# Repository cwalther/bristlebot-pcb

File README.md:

# Capacitor-Powered Bristlebot Kit

Eagle PCB files for
[http://wiki.fablabwinti.ch/Capacitor-Powered_Bristlebot_Kit](http://wiki.fablabwinti.ch/Capacitor-Powered_Bristlebot_Kit).

© 2016 Christian Walther, licensed [CC BY-SA 4.0](http://creativecommons.org/licenses/by-sa/4.0/).

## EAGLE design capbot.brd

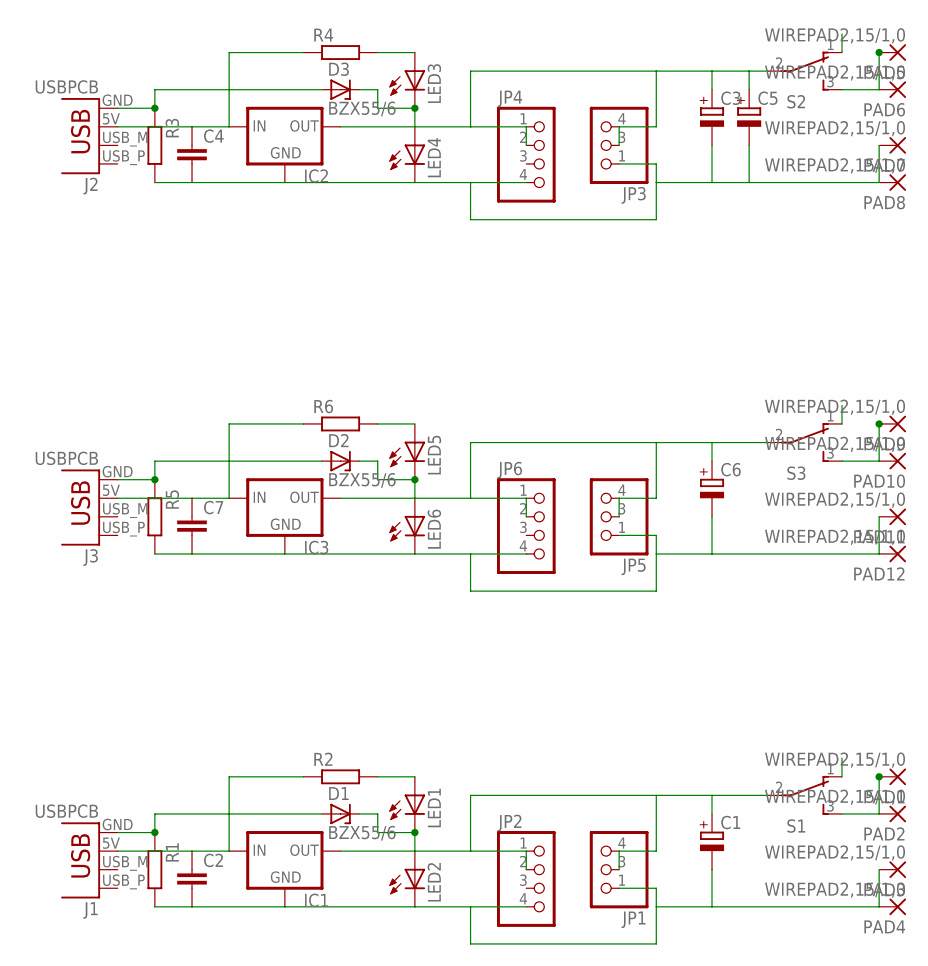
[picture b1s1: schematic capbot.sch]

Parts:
C1, C3, C5, C6: CPOL-EUE5-10.5; E5-10,5
C2, C4, C7: C-EUC1206; C1206
D1, D2, D3: BZX55/6; DO35Z6
IC1, IC2, IC3: MCP1700INLINE; TO92-INLINE
J1, J2, J3: USBPCB; USB-A-PCB
JP1, JP3, JP5: PINHD-1X3-4GAP; 1X04/GAP2
JP2, JP4, JP6: PINHD-1X4; 1X04/OFFSETDOWN
LED1, LED2, LED3, LED4, LED5, LED6: LED3MM-MOREFLAT
PAD1, PAD2, PAD3, PAD4, PAD5, PAD6, PAD7, PAD8, PAD9, PAD10, PAD11, PAD12: WIREPAD2,15/1,0; 2,15/1,0
R1, R2, R3, R4, R5, R6: R-EU_0207/7; 0207/7
S1, S2, S3: TL36PO; TL3XPO

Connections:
unnamed: C1.-, C2.2, IC1.1 (GND), JP1.1, JP2.4, LED2.K (C), PAD3.1, PAD4.1, R1.2
unnamed: C1.+, IC1.3 (OUT), JP1.3 (2), JP1.4 (3), JP2.1, JP2.2, S1.2
unnamed: PAD1.1, PAD2.1, S1.3 (S)
unnamed: D1.A, J1.GND, R1.1
unnamed: C2.1, IC1.2 (IN), J1.5V (VBUS), R2.1
unnamed: LED1.A, R2.2
unnamed: D1.C, LED1.K (C), LED2.A
unnamed: C3.-, C4.2, C5.-, IC2.1 (GND), JP3.1, JP4.4, LED4.K (C), PAD7.1, PAD8.1, R3.2
unnamed: C3.+, C5.+, IC2.3 (OUT), JP3.3 (2), JP3.4 (3), JP4.1, JP4.2, S2.2
unnamed: PAD5.1, PAD6.1, S2.3 (S)
unnamed: D3.A, J2.GND, R3.1
unnamed: C4.1, IC2.2 (IN), J2.5V (VBUS), R4.1
unnamed: LED3.A, R4.2
unnamed: D3.C, LED3.K (C), LED4.A
unnamed: C6.-, C7.2, IC3.1 (GND), JP5.1, JP6.4, LED6.K (C), PAD11.1, PAD12.1, R5.2
unnamed: C6.+, IC3.3 (OUT), JP5.3 (2), JP5.4 (3), JP6.1, JP6.2, S3.2
unnamed: PAD9.1, PAD10.1, S3.3 (S)
unnamed: D2.A, J3.GND, R5.1
unnamed: C7.1, IC3.2 (IN), J3.5V (VBUS), R6.1
unnamed: LED5.A, R6.2
unnamed: D2.C, LED5.K (C), LED6.A

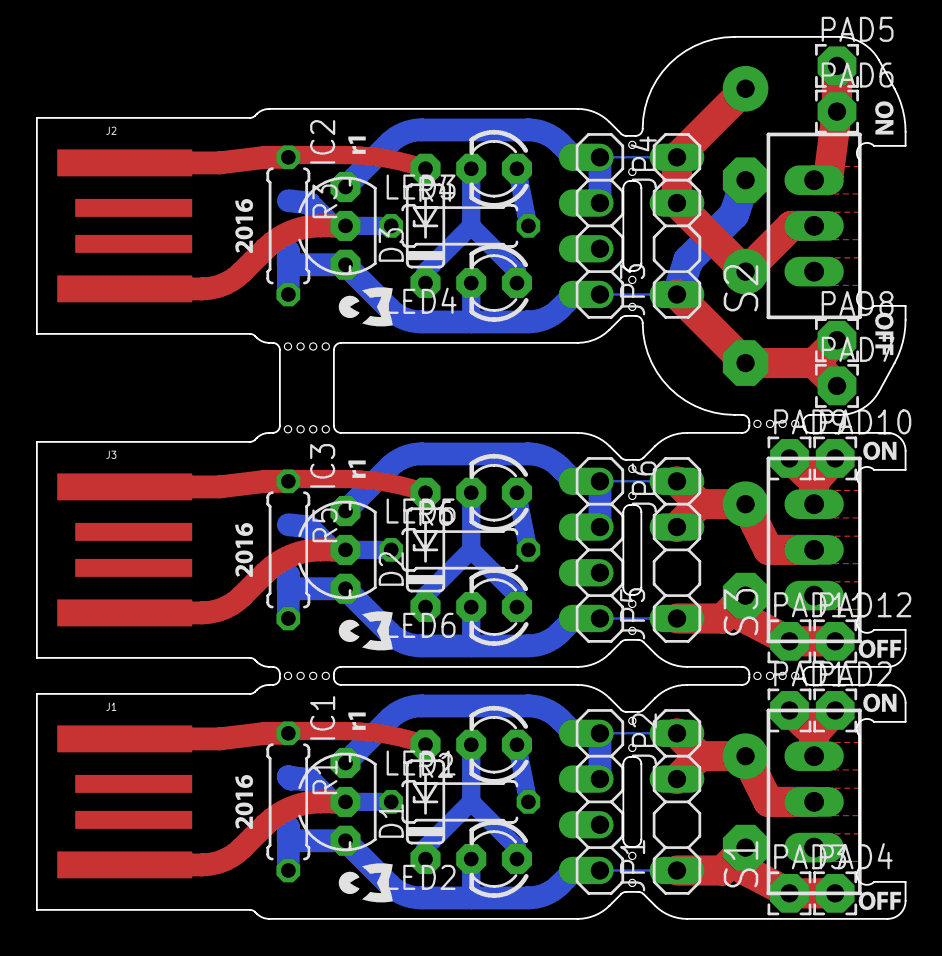
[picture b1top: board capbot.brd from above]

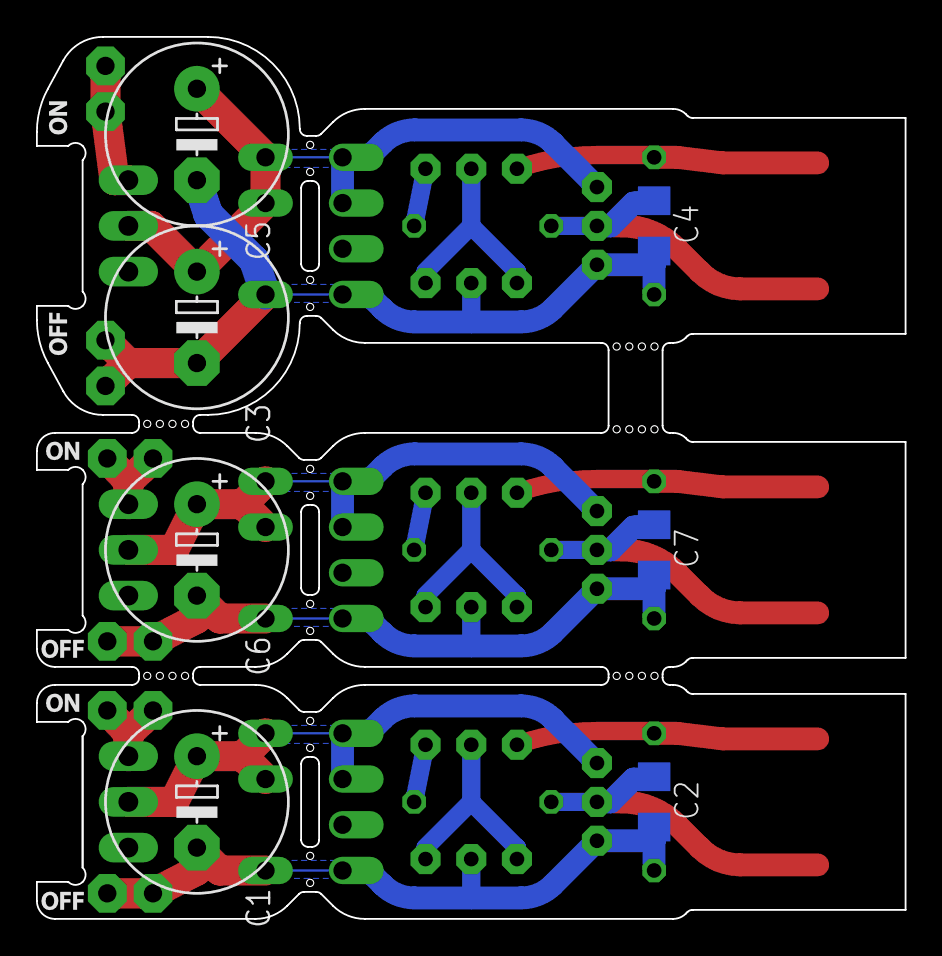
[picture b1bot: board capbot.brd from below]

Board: 2 copper layers, 48.2 x 49.0 mm, 70 parts (13 on the bottom side), 21 nets.

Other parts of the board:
U$1, U$2, U$8: CWLOGO-3
U$3, U$5, U$9: 2016
U$4, U$6, U$10: R1
U$7, U$12, U$14, U$16, U$18, U$20: OFF
U$11, U$13, U$15, U$17, U$19, U$21: ON

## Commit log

2016-08-06 WIP 1
2016-08-10 Stretch the charger part by 0.2 in.
    This goes against my natural tendency to make things as small as possible, but in this case the added length has some advantages:
    - It allows the use of a straight instead of angled pin header if desired, without the switch getting in the way of the USB port.
    - It makes things a bit easier to solder for beginners.
2016-08-10 Move the pin header 0.8 mm closer to the edge so that the horizontal part of the wires can sit flush to the surface with less bending and filing.
    This required changing the pads from "long" to "offset" to prevent them from getting too close to the edge. Unfortunately it seems a pad can only be offset all the way, the drill position is not cont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
2016-08-10 Enlarge the solder pads of the LEDs a little to make them easier to solder.
    They are the same size as the ones of the voltage regulator now.
    Curiously enough, the resistors had the same pad size but I didn't find them as problematic. Leaving them alone for now.
2016-08-11 Add power LED function.
    With one added Zener diode, the top LED indicates that the device is powered, while both LEDs together still indicate that charging is completed.
2016-08-11 Get rid of a via by using an existing hole, and some other prettifications.
2016-08-11 Replace the zero-line-width silkscreen polygons by ones made for 0.15 mm line width.
    Previously, they needlessly inflated the Gerber file size because Eagle apparently uses lines of the same width as the outline to fill them, resulting in ten-thousands of zero-width lines. The manufa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
2016-09-09 Add readme with license infomation.
2017-07-10 Move PCB files to subfolder.
2017-07-10 Instructions for r1.
2017-07-10 Instructions for r2.
2017-07-10 Extend instructions with pictures of various configurations.
    And other minor clarifications.

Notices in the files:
parts and their libraries:
SparkFun-Connectors: Licensing: Creative Commons ShareAlike 4.0 International - https://creativecommons.org/licenses/by-sa/4.0
